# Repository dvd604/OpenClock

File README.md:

# OpenClock
Raspberry Pi Pico / ESPHome based central heating controller

# Background
I bought a house that had a "dumb" heating controller - a heating clock that switched zones on and off on a schedule. It had three zones, as my house has a hot water, upstairs and downstairs loop.
I replaced it for a Nest Learning Thermostat 3, and was very unimpressed with it - It only had water and one zone, and the app design was terrible. For me (having an oil fired boilder), I wanted to turn the heating on for an hour in the morning to get the house warm, and give me hot water for a shower, and that's about it. Obviously as the name suggests, the Nest Thermostat wanted to get the house to a temperature and hold it there, which didn't work for me.

To fix this, I designed OpenClock - an ESPHome based heating clock built around readily available parts that would integrate into my already mature smart home system, giving me the ability to make the control of this clock as simple or as complex as I wanted. It was also a learning tool for me, being the second time I've designed circuitry for UK mains (240V) applications.

While I wouldn't recommend anyone build this (as I have limited experience with designing mains application devices), and this repo is more for demonstration purposes, I have been using OpenClock for over a year without issue.

# Features

* Designed to screw to a UK single gang backbox
* 3 Heating zones, can be switched on and off independantly
* Runs ESPHome on a RPi Pico, so firmware can be modified

# Heating systems known to work

Only tested in my house - has an oil fired boiler, which is controlled in two ways:

1. The water "zone" sends mains power directly to the water "zone" valve - this valve opens, and a switch inside the valve then powers the boiler.
2. The room "zones" send mains power to a room thermostat - this thermostat has the final say over whether the room "zone" valve opens, which when opened, powers the boiler as above.
 
# The benefit of hindsight

While OpenClock has worked well for over a year, having spent some time with it, I now know how I would do it different - and probably will. If I was doing this centralised control method again, I would buy a Shelly relay - these guys have far more experience than me with designing safe electronics, and their hardware is small enough to fit in a UK backbox. One of their relays probably costs less than the price of the PCBs alone.

However, I've come to strongly dislike my room thermostats - they're loud when switching, difficult to use, and are very feature-light. By this I mean, they turn on and off with temperature in a room.
To fix this, I would hardwire the mains wires where OpenClock is at the moment, so the room thermostats are receiving power all the time, and install something like the Sonoff NSPanel. This would add so many more options into the rooms where the thermostats are mounted.

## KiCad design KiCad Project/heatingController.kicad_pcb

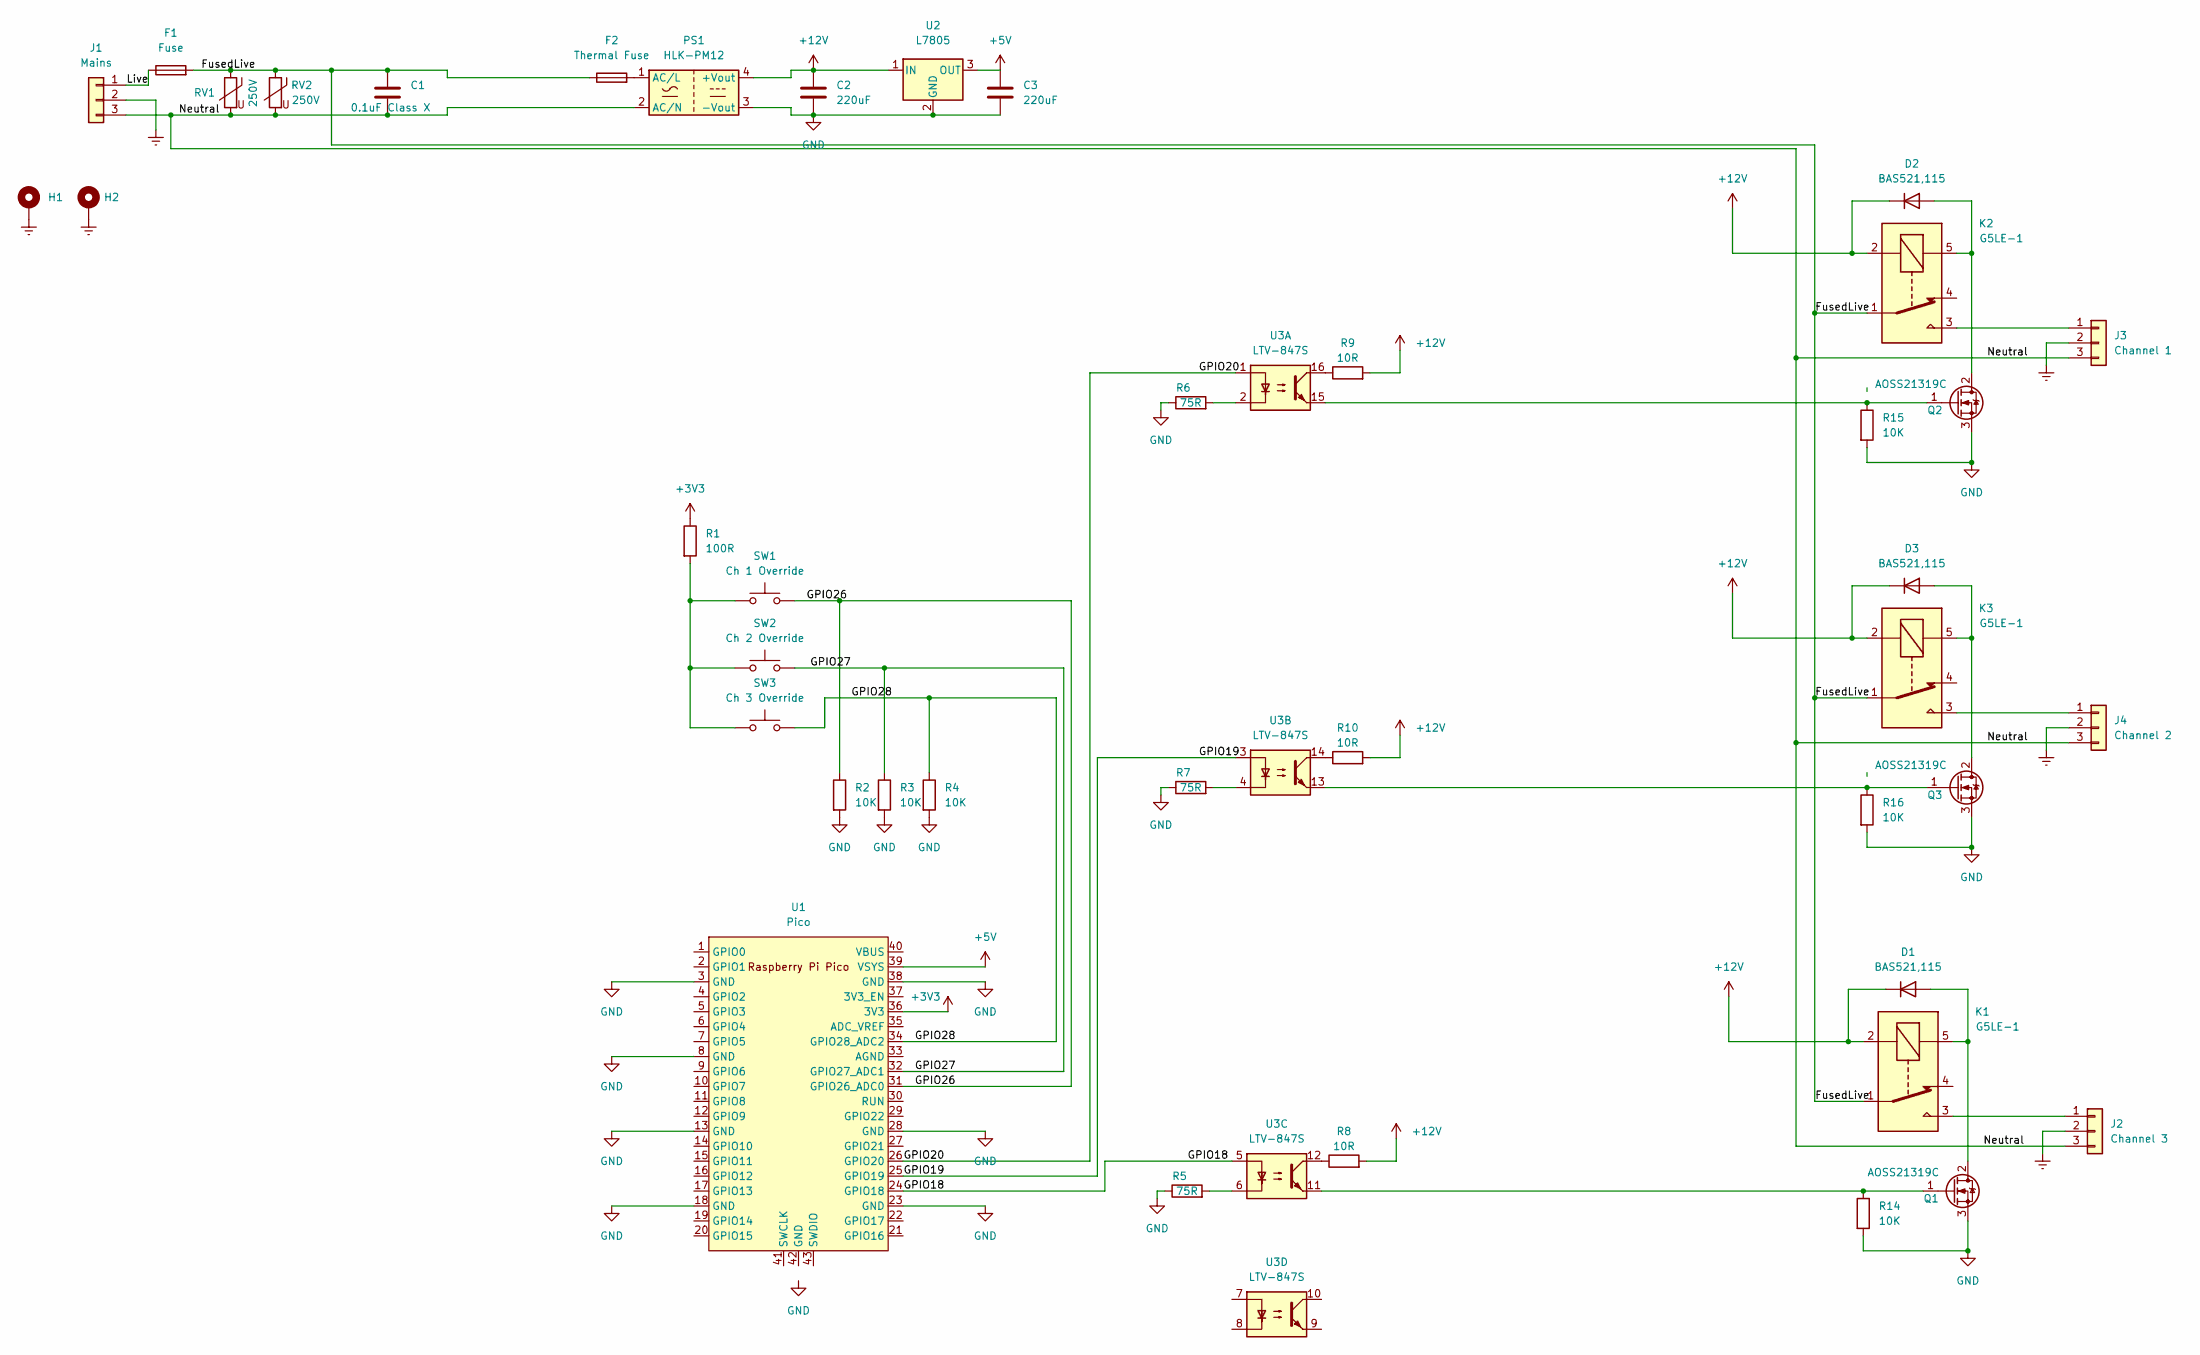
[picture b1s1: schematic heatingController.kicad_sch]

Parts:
C1: 0.1uF Class X; C_Rect_L18.0mm_W8.0mm_P15.00mm_FKS3_FKP3
C2, C3: 220uF; R_0603_1608Metric_Pad0.98x0.95mm_HandSolder
D1, D2, D3: BAS521,115; D_SOD-523
F1: Fuse; Fuse_BelFuse_0ZRE0100FF_L18.7mm_W5.1mm
F2: Thermal Fuse; PhoenixContact_MSTBVA_2,5_2-G-5,08_1x02_P5.08mm_Vertical
H1, H2: 1; MountingHole_3.2mm_M3_Pad
J1: Mains; PhoenixContact_MSTBVA_2,5_3-G-5,08_1x03_P5.08mm_Vertical
J2: Channel 3; PhoenixContact_MSTBVA_2,5_3-G-5,08_1x03_P5.08mm_Vertical
J3: Channel 1; PhoenixContact_MSTBVA_2,5_3-G-5,08_1x03_P5.08mm_Vertical
J4: Channel 2; PhoenixContact_MSTBVA_2,5_3-G-5,08_1x03_P5.08mm_Vertical
K1, K2, K3: G5LE-1; Relay_SPDT_Omron-G5LE-1
PS1: HLK-PM12; Converter_ACDC_HiLink_HLK-PMxx
Q1, Q2, Q3: AOSS21319C; SOT-23
R1: 100R; R_0603_1608Metric_Pad0.98x0.95mm_HandSolder
R2, R3, R4, R14, R15, R16: 10K; R_0603_1608Metric_Pad0.98x0.95mm_HandSolder
R5, R6, R7: 75R; R_0805_2012Metric_Pad1.20x1.40mm_HandSolder
R8, R9, R10: 10R; R_0805_2012Metric_Pad1.20x1.40mm_HandSolder
RV1, RV2: 250V; RV_Disc_D12mm_W3.9mm_P7.5mm
SW1: Ch 1 Override; PinSocket_1x02_P2.54mm_Vertical
SW2: Ch 2 Override; PinSocket_1x02_P2.54mm_Vertical
SW3: Ch 3 Override; PinSocket_1x02_P2.54mm_Vertical
U1: Pico; RPi_Pico_SMD_TH
U2: L7805; TO-252-3_TabPin2
U3: LTV-847S; SMDIP-16_W9.53mm

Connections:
+3V3: R1.1, U1.36 (3V3)
+5V: C3.1, U1.39 (VSYS), U2.3 (OUT)
+12V: C2.1, D1.1 (K), D2.1 (K), D3.1 (K), K1.2, K2.2, K3.2, PS1.4 (+Vout), R8.2, R9.2, R10.2, U2.1 (IN)
/FusedLive: C1.1, F1.2, F2.1, K1.1, K2.1, K3.1, RV1.1, RV2.1
/GPIO18: U1.24 (GPIO18), U3.5
/GPIO19: U1.25 (GPIO19), U3.3
/GPIO20: U1.26 (GPIO20), U3.1
/GPIO26: R2.1, SW1.2, U1.31 (GPIO26_ADC0)
/GPIO27: R3.1, SW2.2, U1.32 (GPIO27_ADC1)
/GPIO28: R4.1, SW3.2, U1.34 (GPIO28_ADC2)
/Live: F1.1, J1.1
/Neutral: C1.2, J1.3, J2.3, J3.3, J4.3, PS1.2 (AC/N), RV1.2, RV2.2
Earth: H1.1, H2.1, J1.2, J2.2, J3.2, J4.2
GND: C2.2, C3.2, PS1.3 (-Vout), Q1.3 (S), Q2.3 (S), Q3.3 (S), R2.2, R3.2, R4.2, R5.1, R6.1, R7.1, R14.2, R15.2, R16.2, U1.3 (GND), U1.8 (GND), U1.13 (GND), U1.18 (GND), U1.23 (GND), U1.28 (GND), U1.38 (GND), U2.2 (GND)
unnamed: D1.2 (A), K1.5, Q1.2 (D)
unnamed: D2.2 (A), K2.5, Q2.2 (D)
unnamed: D3.2 (A), K3.5, Q3.2 (D)
unnamed: F2.2, PS1.1 (AC/L)
unnamed: J2.1, K1.3
unnamed: J3.1, K2.3
unnamed: J4.1, K3.3
unnamed: Q1.1 (G), R14.1, U3.11
unnamed: Q2.1 (G), R15.1, U3.15
unnamed: Q3.1 (G), R16.1, U3.13
unnamed: R1.2, SW1.1, SW2.1, SW3.1
unnamed: R5.2, U3.6
unnamed: R6.2, U3.2
unnamed: R7.2, U3.4
unnamed: R8.1, U3.12
unnamed: R9.1, U3.16
unnamed: R10.1, U3.14

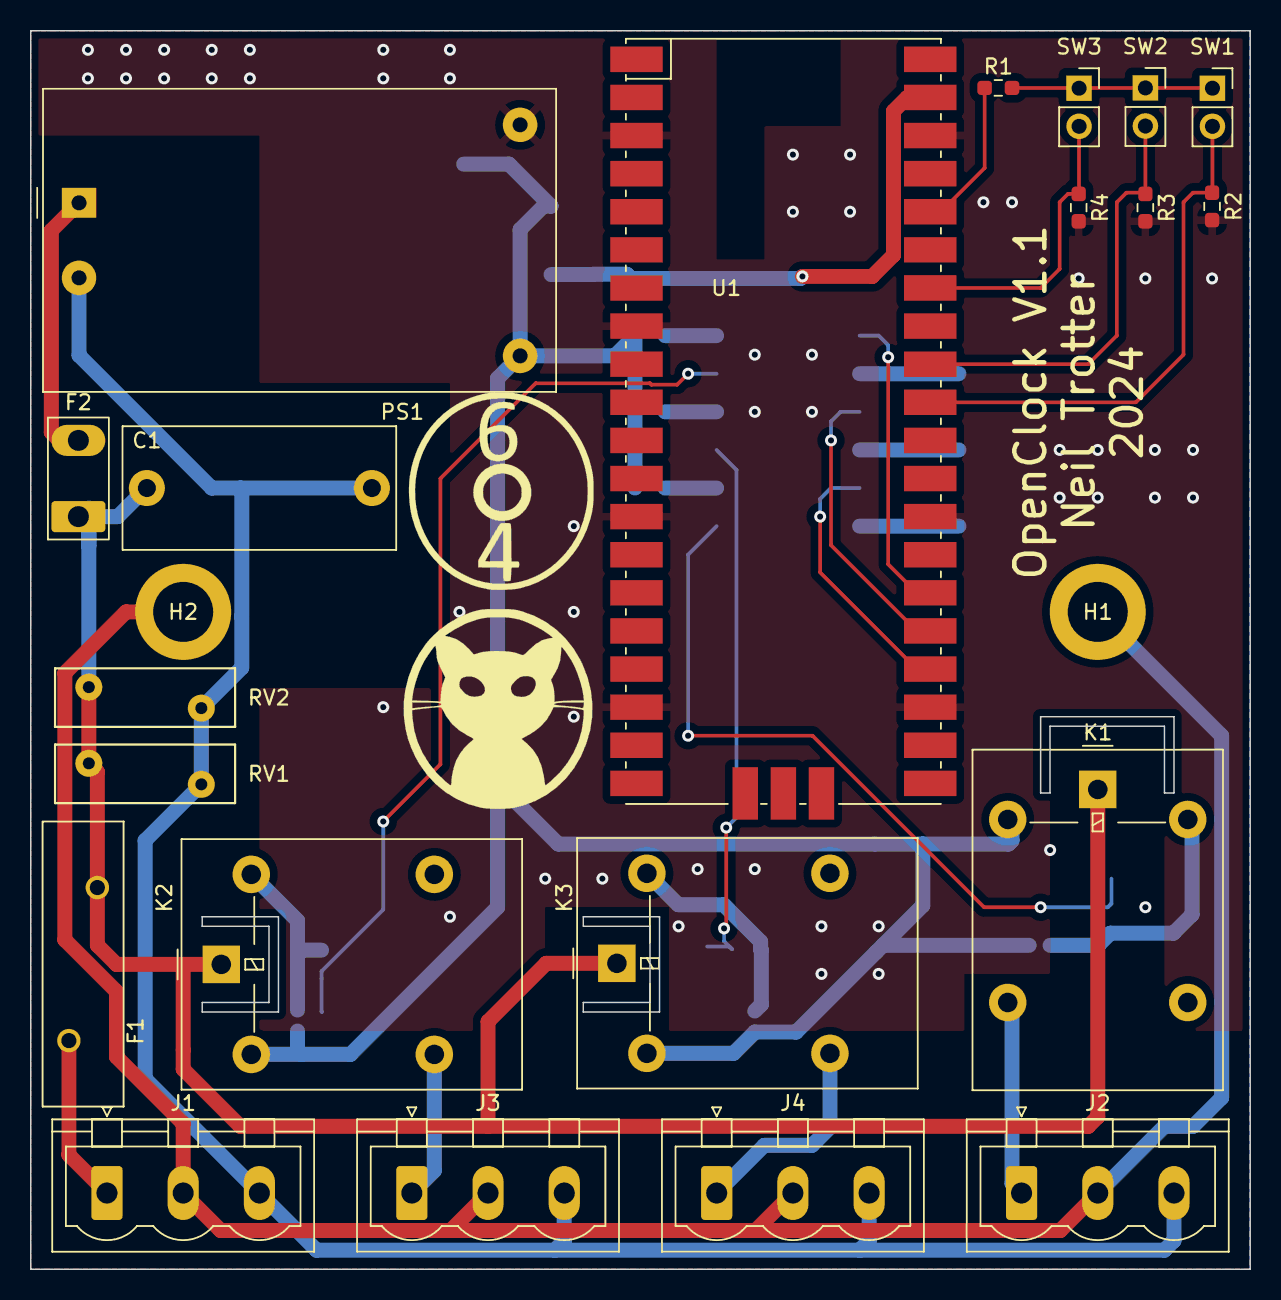
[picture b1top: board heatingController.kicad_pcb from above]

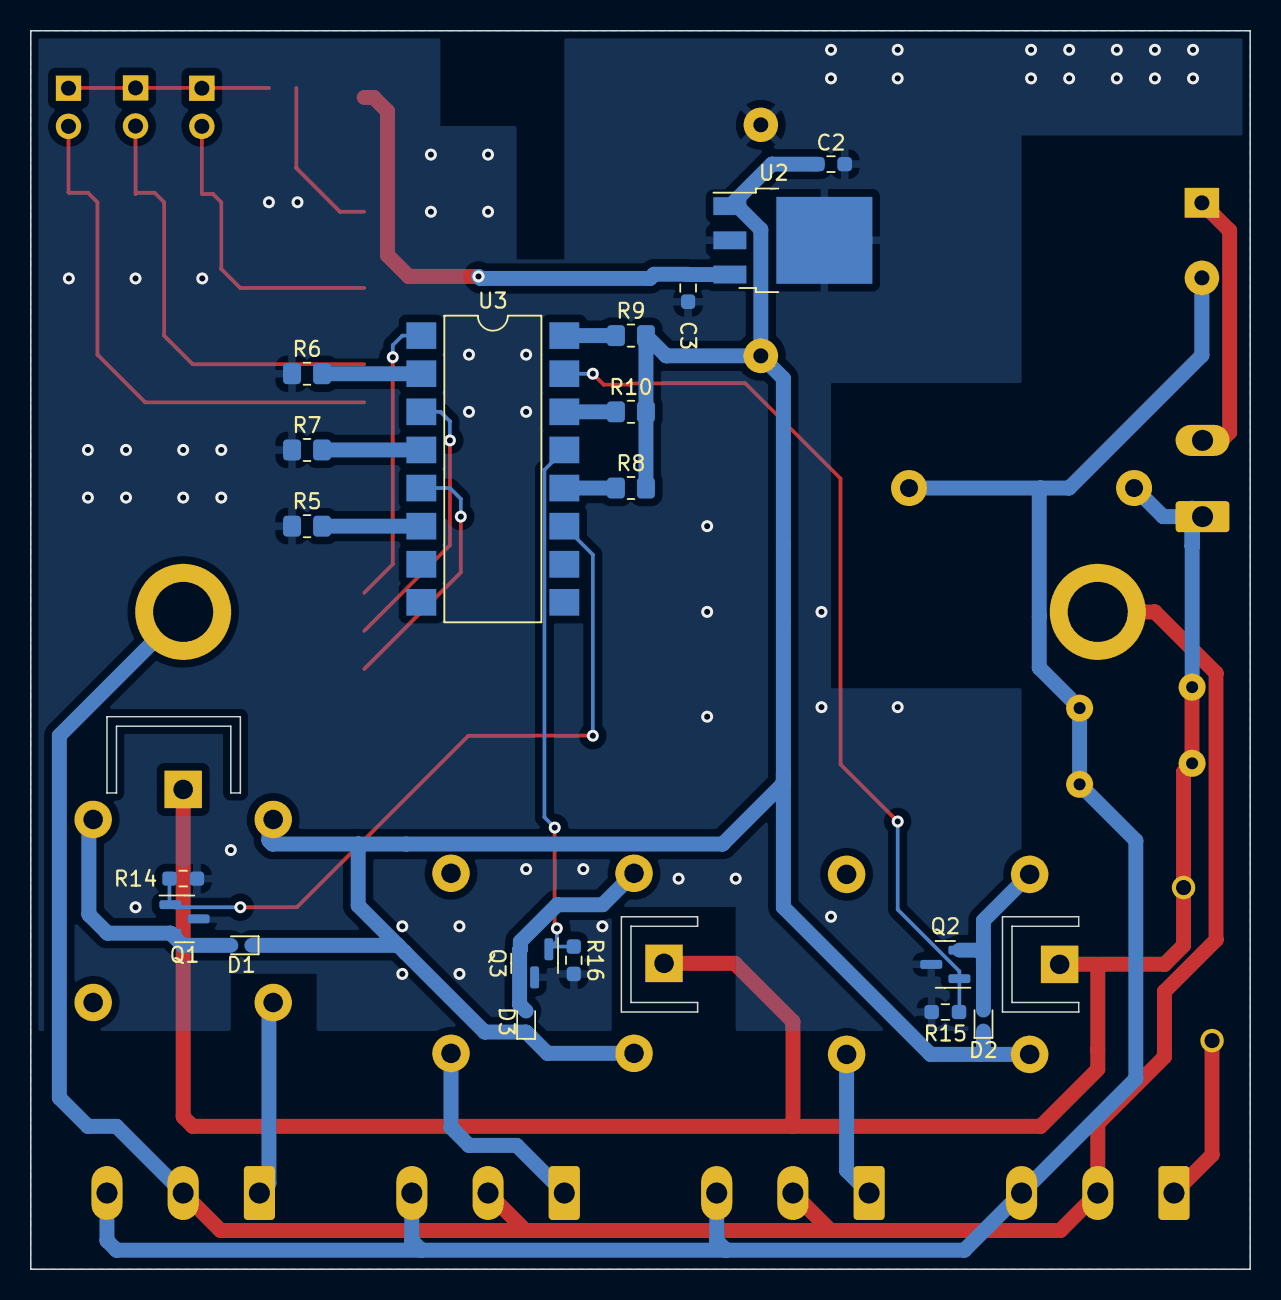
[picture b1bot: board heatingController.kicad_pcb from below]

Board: 2 copper layers, 81.3 x 82.6 mm, 42 parts (19 on the bottom side), 31 nets.

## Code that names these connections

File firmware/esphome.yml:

esphome:
  name: openclock
  friendly_name: OpenClock

rp2040:
  board: rpipicow

# Enable logging
logger:
  level: INFO

# Enable Home Assistant API
api:
  encryption:
    key: ""

wifi:
  ssid: !secret wifi_ssid
  password: !secret wifi_password
  
  ap:
    ssid: "Openclock Fallback Hotspot"
    password: ""
    
ota:
  - platform: esphome
    password: ""

globals:
  - id: upstairs_ticks
    type: int
    restore_value: no
    initial_value: "0"
  - id: downstairs_ticks
    type: int
    restore_value: no
    initial_value: "0"
  - id: water_ticks
    type: int
    restore_value: no
    initial_value: "0"

binary_sensor:
  - platform: gpio
    pin: GPIO26
    name: "HW Switch 1"
    id: "hw_switch_1"
    internal: True
    filters:
      - delayed_on: 100ms
    entity_category: "diagnostic"
    on_state: 
      then:
        - lambda: |-
            id(auto_off).turn_on();
            if(id(hw_switch_1).state){

              auto call = id(upstairs_limit).make_call();
              call.number_increment(true);
              call.perform();


            //  id(upstairs_switch).turn_on();
            }

  - platform: gpio
    pin: GPIO27
    name: "HW Switch 2"
    id: "hw_switch_2"
    internal: True
    filters:
      - delayed_on: 100ms
    entity_category: "diagnostic"
    on_state: 
      then:
        - lambda: |-
            id(auto_off).turn_on();
            if(id(hw_switch_2).state){
              
              auto call = id(downstairs_limit).make_call();
              call.number_increment(true);
              call.perform();


             // id(downstairs_switch).turn_on();
            }

  - platform: gpio
    pin: GPIO28
    name: "HW Switch 3"
    id: "hw_switch_3"
    internal: True
    filters:
      - delayed_on: 100ms
    entity_category: "diagnostic"
    on_state: 
      then:
        - lambda: |-
            id(auto_off).turn_on();
            if(id(hw_switch_3).state){

              auto call = id(water_limit).make_call();
              call.number_increment(true);
              call.perform();
              
              //id(water_switch).turn_on();
            }

number:
  - platform: template
    name: "Upstairs duration"
    icon: "mdi:clock-edit"
    id: upstairs_limit
    step: 15
    min_value: 15
    max_value: 120
    optimistic: true
    entity_category: "config"
    unit_of_measurement: "minutes"
  - platform: template
    name: "Downstairs duration"
    icon: "mdi:clock-edit"
    id: downstairs_limit
    step: 15
    min_value: 15
    max_value: 120
    optimistic: true
    entity_category: "config"
    unit_of_measurement: "minutes"
  - platform: template
    name: "Water duration"
    icon: "mdi:clock-edit"
    id: water_limit
    step: 15
    min_value: 15
    max_value: 120
    optimistic: true
    entity_category: "config"
    unit_of_measurement: "minutes"

text_sensor:
  - platform: template
    name: "Upstairs On-Time"
    id: up_ticks_sensor
    entity_category: "diagnostic"
    lambda: 'return {std::to_string(id(upstairs_ticks)/60) + ":" + std::to_string(id(upstairs_ticks)%60)};'
    update_interval: 10s

  - platform: template
    name: "Downstairs On-Time"
    id: down_ticks_sensor
    entity_category: "diagnostic"
    lambda: 'return {std::to_string(id(downstairs_ticks)/60) + ":" + std::to_string(id(downstairs_ticks)%60)};'
    update_interval: 10s

  - platform: template
    name: "Water On-Time"
    id: water_ticks_sensor
    entity_category: "diagnostic"
    lambda: 'return {std::to_string(id(water_ticks)/60) + ":" + std::to_string(id(water_ticks)%60)};'
    update_interval: 10s

switch:
  - platform: restart
    name: "Restart"
    entity_category: "diagnostic"
  - platform: template
    name: "Upstairs heating"
    id: upstairs_switch
    icon: "mdi:radiator"
    restore_mode: ALWAYS_OFF
    optimistic: True
    on_turn_on: 
      output.turn_on: relay_upstairs
    on_turn_off: 
      output.turn_off: relay_upstairs

  - platform: template
    name: "Downstairs heating"
    id: downstairs_switch
    icon: "mdi:radiator"
    restore_mode: ALWAYS_OFF
    optimistic: True
    on_turn_on: 
      - output.turn_on: relay_downstairs
    on_turn_off: 
      - output.turn_off: relay_downstairs

  - platform: template
    name: "Water heater"
    id: water_switch
    icon: "mdi:water"
    optimistic: True
    restore_mode: ALWAYS_OFF
    on_turn_on: 
      - output.turn_on: relay_water
    on_turn_off: 
      - output.turn_off: relay_water

  - platform: template
    name: "Enable Auto-Off"
    id: auto_off
    optimistic: True
    device_class: "switch"
    entity_category: "config"
    restore_mode: ALWAYS_ON
    on_turn_on: 
      then:
        - lambda: id(timer_tick).execute();
    on_turn_off: 
      then:
        - lambda: |-
            id(timer_tick).stop();
            id(water_ticks) = 0;
            id(upstairs_ticks) = 0;
            id(downstairs_ticks) = 0;

sensor:
  - platform: adc
    pin: TEMPERATURE
    name: "Core Temperature"
    entity_category: "diagnostic"
    unit_of_measurement: "°C"
    filters:
      - lambda: return 27 - (x - 0.706f) / 0.001721f;
  - platform: adc
    pin: VCC
    name: "VCC Voltage"
    unit_of_measurement: "V"
    entity_category: "diagnostic"

output:
  - platform: gpio
    id: relay_upstairs
    pin: GPIO18
    inverted: true
  - platform: gpio
    id: relay_downstairs
    pin: GPIO19
    inverted: true
  - platform: gpio
    id: relay_water
    pin: GPIO20
    inverted: true

script:
  - id: timer_tick
    mode: queued
    then:
      - delay: 1s
      - lambda: |-
            //if(!id(auto_off).state) return;

            if(id(upstairs_switch).state) {
              id(upstairs_ticks) ++;
            } else {
              id(upstairs_ticks) = 0;
            }

            if(id(downstairs_switch).state) {
              id(downstairs_ticks) ++;
            } else {
              id(downstairs_ticks) = 0;
            }

            if(id(water_switch).state) {
              id(water_ticks) ++;
            } else {
              id(water_ticks) = 0;
            }

            if(id(water_ticks) >= id(water_limit).state * 60){
              id(relay_water).turn_off();
              id(water_switch).turn_off();
              id(water_ticks) = 0;
            }

            if(id(upstairs_ticks) >= id(upstairs_limit).state * 60){
              id(relay_upstairs).turn_off();
              id(upstairs_switch).turn_off();
              id(upstairs_ticks) = 0;
            }

            if(id(downstairs_ticks) >= id(downstairs_limit).state * 60){
              id(relay_downstairs).turn_off();
              id(downstairs_switch).turn_off();
              id(downstairs_ticks) = 0;
            } 

            id(timer_tick).execute();
